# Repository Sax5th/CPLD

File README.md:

# CPLD
based on xilinx XC9536XL

Breakout Board Inspo:https://github.com/hotkeysoft/xc9536xlBreakout-kicad

C.O.T.S Version: http://dangerousprototypes.com/docs/XC9500XL_CPLD_breakout_board

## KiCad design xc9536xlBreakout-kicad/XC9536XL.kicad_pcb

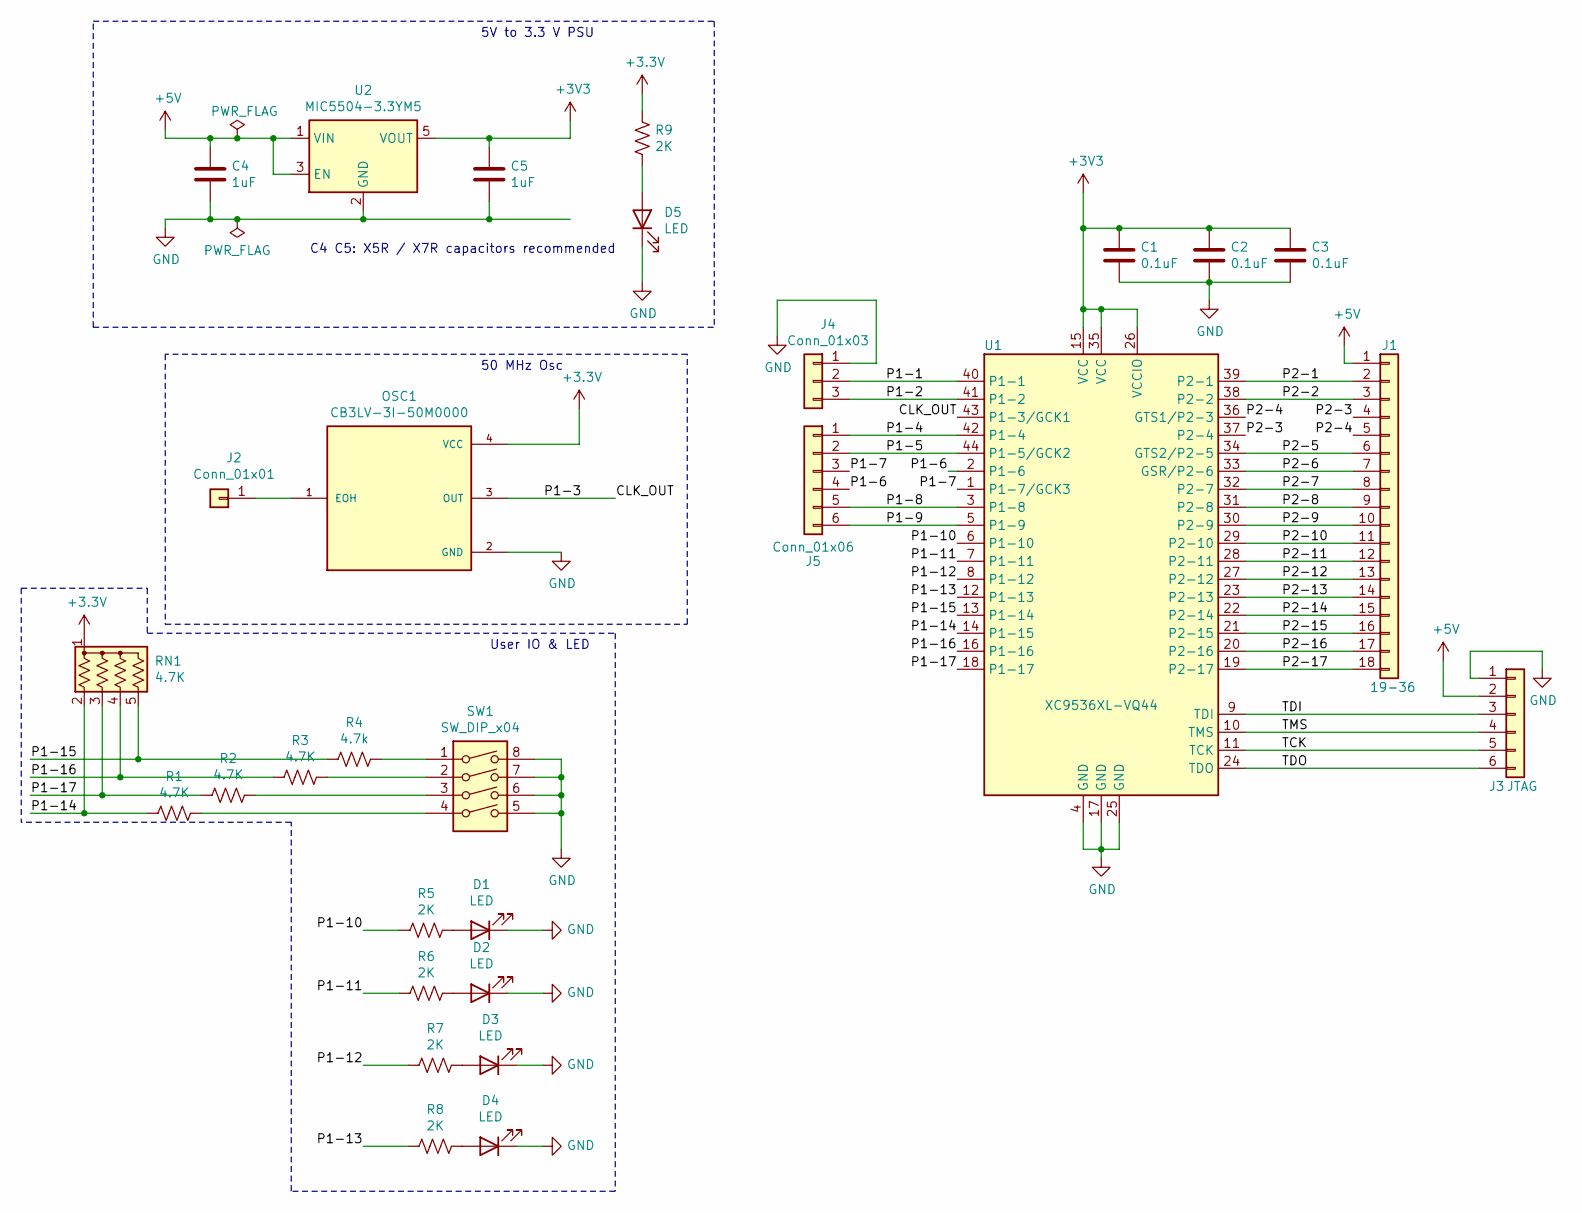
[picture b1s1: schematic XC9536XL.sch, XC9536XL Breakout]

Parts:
C1, C2, C3: 0.1uF; C_0603_1608Metric
C4, C5: 1uF; C_0603_1608Metric
D1, D2, D3, D4, D5: LED; D_0805_2012Metric_Pad1.15x1.40mm_HandSolder
J1: 19-36; PinHeader_1x18_P2.54mm_Vertical
J2: Conn_01x01; PinHeader_1x01_P2.54mm_Vertical
J3: JTAG; PinHeader_1x06_P2.54mm_Vertical
J4: Conn_01x03; PinHeader_1x03_P2.54mm_Vertical
J5: Conn_01x06; PinHeader_1x06_P2.54mm_Vertical
OSC1: CB3LV-3I-50M0000; OSCCC700X500X180-4N
R1, R2, R3: 4.7K; R_0805_2012Metric_Pad1.20x1.40mm_HandSolder
R4: 4.7k; R_0805_2012Metric_Pad1.20x1.40mm_HandSolder
R5, R6, R7, R8, R9: 2K; R_0805_2012Metric_Pad1.20x1.40mm_HandSolder
RN1: 4.7K; R_Array_Convex_4x1206
SW1: SW_DIP_x04; SW_DIP_SPSTx04_Slide_6.7x11.72mm_W8.61mm_P2.54mm_LowProfile
U1: XC9536XL-VQ44; TQFP-44_10x10mm_P0.8mm
U2: MIC5504-3.3YM5; SOT-23-5

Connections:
+5V: C4.1, J1.1, J3.2, U2.1 (VIN), U2.3 (EN)
/CLK_OUT: OSC1.3 (OUT), U1.43 (P1-3/GCK1)
/P1-1: J4.2, U1.40 (P1-1)
/P1-2: J4.3, U1.41 (P1-2)
/P1-4: J5.1, U1.42 (P1-4)
/P1-5: J5.2, U1.44 (P1-5/GCK2)
/P1-6: J5.4, U1.2 (P1-6)
/P1-7: J5.3, U1.1 (P1-7/GCK3)
/P1-8: J5.5, U1.3 (P1-8)
/P1-9: J5.6, U1.5 (P1-9)
/P1-10: R5.2, U1.6 (P1-10)
/P1-11: R6.2, U1.7 (P1-11)
/P1-12: R7.2, U1.8 (P1-12)
/P1-13: R8.2, U1.12 (P1-13)
/P1-14: R1.2, RN1.2 (R1), U1.14 (P1-15)
/P1-15: R4.2, RN1.5 (R4), U1.13 (P1-14)
/P1-16: R3.2, RN1.4 (R3), U1.16 (P1-16)
/P1-17: R2.2, RN1.3 (R2), U1.18 (P1-17)
/P2-1: J1.2, U1.39 (P2-1)
/P2-2: J1.3, U1.38 (P2-2)
/P2-3: J1.4, U1.37 (P2-4)
/P2-4: J1.5, U1.36 (GTS1/P2-3)
/P2-5: J1.6, U1.34 (GTS2/P2-5)
/P2-6: J1.7, U1.33 (GSR/P2-6)
/P2-7: J1.8, U1.32 (P2-7)
/P2-8: J1.9, U1.31 (P2-8)
/P2-9: J1.10, U1.30 (P2-9)
/P2-10: J1.11, U1.29 (P2-10)
/P2-11: J1.12, U1.28 (P2-11)
/P2-12: J1.13, U1.27 (P2-12)
/P2-13: J1.14, U1.23 (P2-13)
/P2-14: J1.15, U1.22 (P2-14)
/P2-15: J1.16, U1.21 (P2-15)
/P2-16: J1.17, U1.20 (P2-16)
/P2-17: J1.18, U1.19 (P2-17)
/TCK: J3.5, U1.11 (TCK)
/TDI: J3.3, U1.9 (TDI)
/TDO: J3.6, U1.24 (TDO)
/TMS: J3.4, U1.10 (TMS)
GND: C1.2, C2.2, C3.2, C4.2, C5.2, D1.1 (K), D2.1 (K), D3.1 (K), D4.1 (K), D5.1 (K), J3.1, J4.1, OSC1.2 (GND), SW1.5, SW1.6, SW1.7, SW1.8, U1.4 (GND), U1.17 (GND), U1.25 (GND), U2.2 (GND)
unnamed: D1.2 (A), R5.1
unnamed: D2.2 (A), R6.1
unnamed: D3.2 (A), R7.1
unnamed: D4.2 (A), R8.1
unnamed: D5.2 (A), R9.2
unnamed: J2.1, OSC1.1 (EOH)
unnamed: R1.1, SW1.4
unnamed: R2.1, SW1.3
unnamed: R3.1, SW1.2
unnamed: R4.1, SW1.1

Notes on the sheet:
C4 C5: X5R / X7R capacitors recommended
5V to 3.3 V PSU
50 MHz Osc
User IO & LED

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
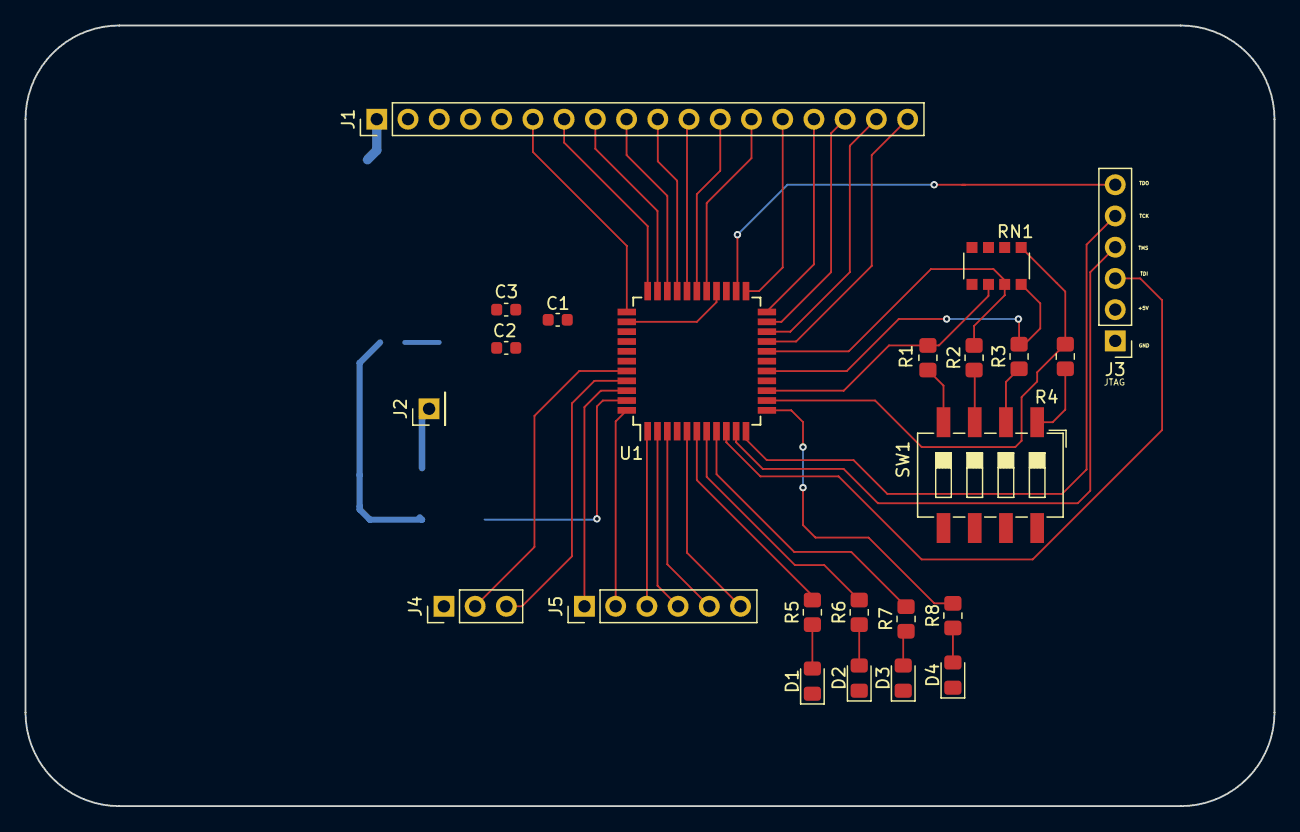
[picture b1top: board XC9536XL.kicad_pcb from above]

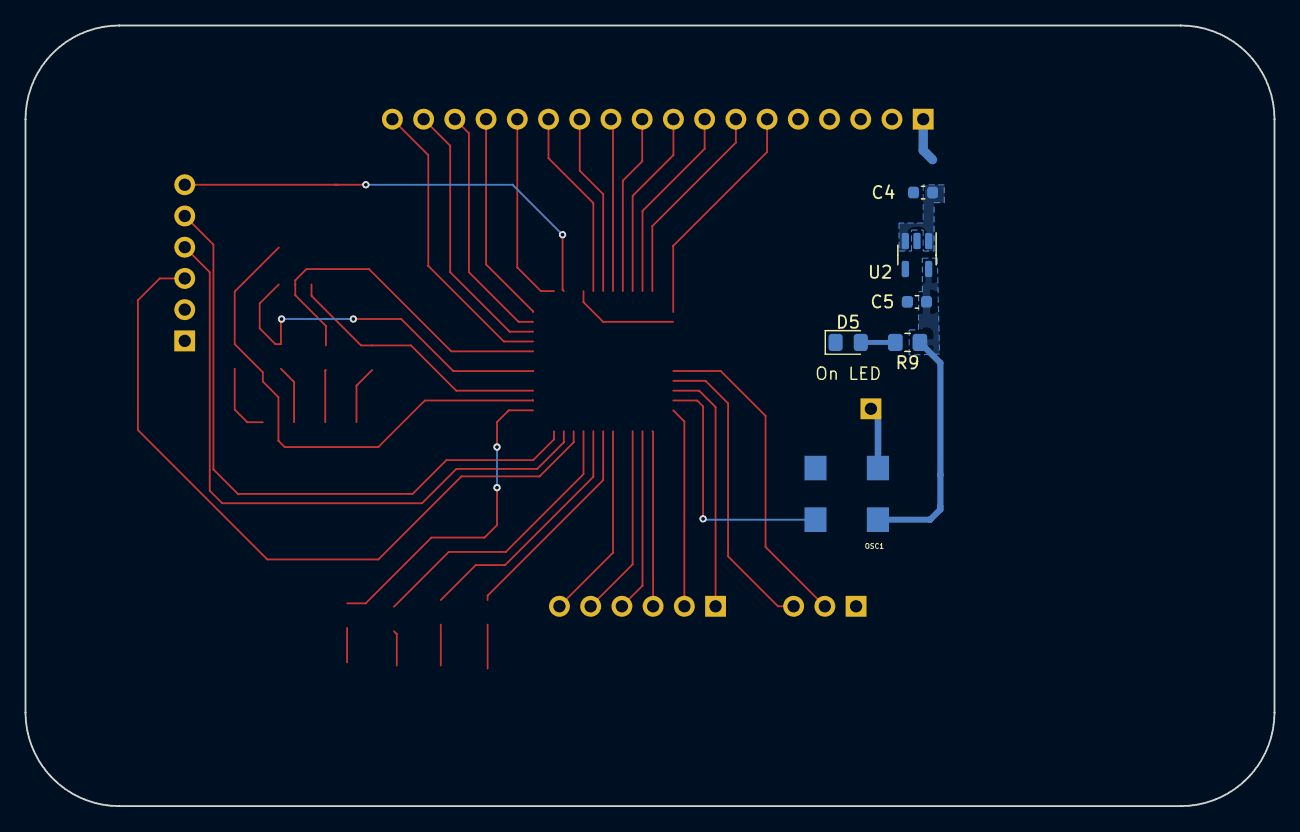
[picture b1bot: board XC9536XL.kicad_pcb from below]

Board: 2 copper layers, 101.6 x 63.5 mm, 29 parts (6 on the bottom side), 51 nets.

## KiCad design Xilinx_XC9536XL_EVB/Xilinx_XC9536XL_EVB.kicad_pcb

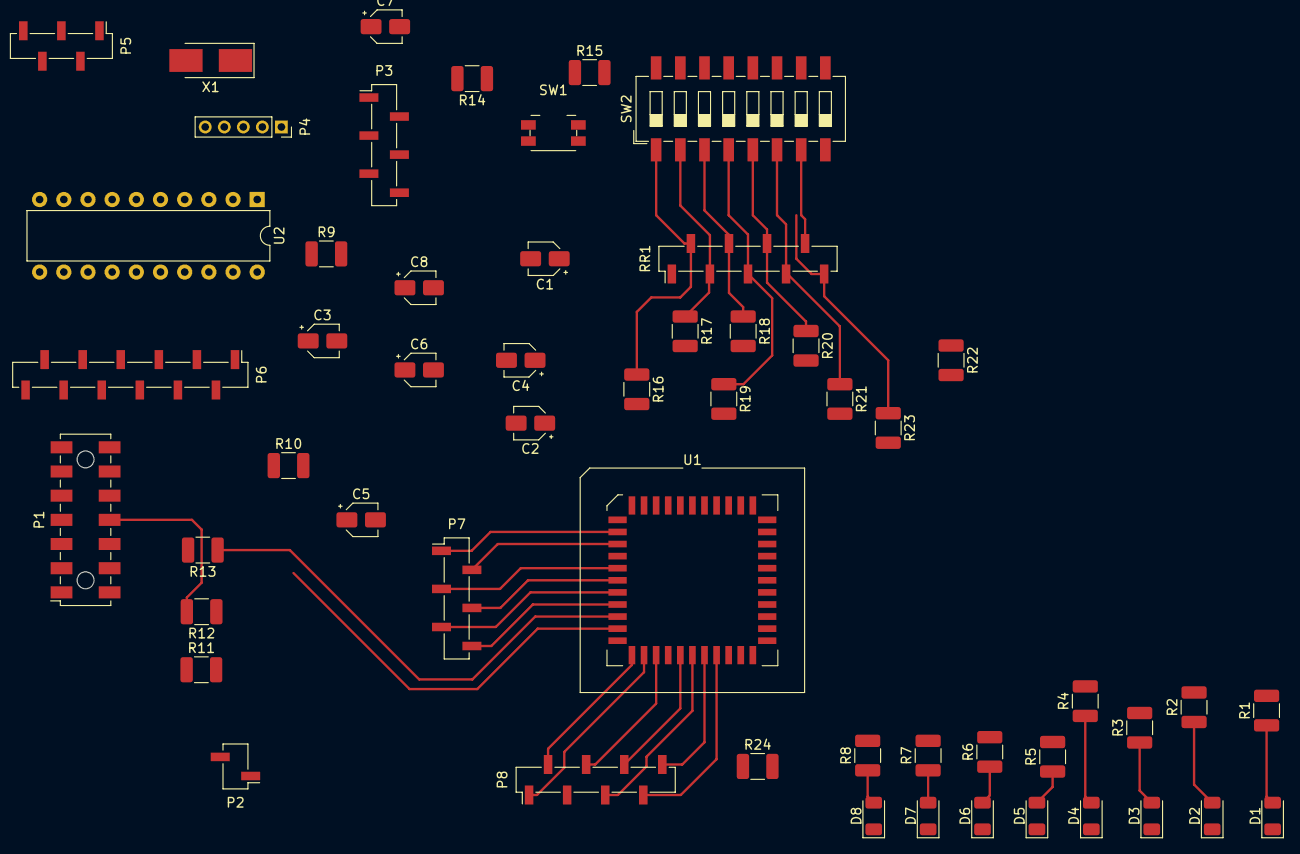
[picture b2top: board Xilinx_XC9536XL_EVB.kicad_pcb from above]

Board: 2 copper layers, 54 parts (0 on the bottom side), 75 nets.

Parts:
C1, C2, C3, C5, C6: 100n; CP_Elec_3x5.4
C4: 10uF; CP_Elec_3x5.4
C7, C8: 22p; CP_Elec_3x5.4
D1, D2, D3, D4, D5, D6, D7, D8: LED; LED_1206_3216Metric
P1: CONN_7X2; Samtec_HLE-107-02-xxx-DV-A_2x07_P2.54mm_Horizontal
P2: CONN_2; PinSocket_1x02_P2.00mm_Vertical_SMD_Pin1Left
P3: CONN_3X2; PinSocket_1x06_P2.00mm_Vertical_SMD_Pin1Left
P4: CONN_5; PinSocket_1x05_P2.00mm_Vertical
P5: CONN_5; PinSocket_1x05_P2.00mm_Vertical_SMD_Pin1Left
P6: CONN_12; PinSocket_1x12_P2.00mm_Vertical_SMD_Pin1Left
P7: CONN_6; PinSocket_1x06_P2.00mm_Vertical_SMD_Pin1Left
P8: CONN_8; PinSocket_1x08_P2.00mm_Vertical_SMD_Pin1Left
R1, R2, R3, R4, R5, R6, R7, R8: 330R; R_1210_3225Metric_Pad1.30x2.65mm_HandSolder
R9: 10k; R_1210_3225Metric_Pad1.30x2.65mm_HandSolder
R10, R11, R12, R13, R24: 0R; R_1210_3225Metric_Pad1.30x2.65mm_HandSolder
R14, R15, R16, R17, R18, R19, R20, R21, R22, R23: 4k7; R_1210_3225Metric_Pad1.30x2.65mm_HandSolder
RR1: 4k7; PinSocket_1x09_P2.00mm_Vertical_SMD_Pin1Left
SW1: SW_PUSH; Panasonic_EVQPUJ_EVQPUA
SW2: SW_DIP_8; SW_DIP_SPSTx08_Slide_6.7x21.88mm_W8.61mm_P2.54mm_LowProfile
U1: XC9536XLPC44; PLCC-44_SMD-Socket
U2: ATtiny2313-20PU; DIP-20_W7.62mm
X1: XTAL; Crystal_SMD_5032-2Pin_5.0x3.2mm_HandSoldering

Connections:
+3.3V: C1.1, C2.1, C3.1, C4.1, P2.1, P4.1, P8.3, R10.1, R24.1, RR1.1, SW1.2, U1.21, U1.32, U1.41
/3V3P: C6.1, P3.2, P6.1, R9.1, R10.2, R11.2, U2.20
/L1: R1.2, U1.36
/L2: R2.2, U1.35
/L3: R3.2, U1.34
/L4: R4.2, U1.33
/L5: R5.2, U1.29
/L6: R6.2, U1.28
/L7: R7.2, U1.27
/L8: R8.2, U1.26
/MISO: P3.1, P6.3, U1.4, U2.18
/MOSI: P3.4, P6.4, U1.6, U2.17
/O1: P8.1, U1.19
/O2: P8.2, U1.18
/O3: P8.4, U1.20
/O4: P8.6, U1.22
/O5: P8.7, U1.25
/O6: P8.8, U1.24
/PD6: P6.10, U2.11
/RESET: P3.5, P4.2, R9.2, U1.2, U2.1
/S1: R16.2, U1.44
/S2: R17.2, U1.1
/S3: R18.2, U1.42
/S4: R19.2, U1.43
/S5: R20.2, U1.40
/S6: R21.2, U1.39
/S7: R22.2, U1.38
/S8: R23.2, U1.37
/SCK: P3.3, P6.2, U1.5, U2.19
/TCK: P1.6, U1.17
/TDI: R13.1, U1.15
/TDO: R12.1, U1.30
/TMS: P1.4, U1.16
GND: C1.2, C2.2, C3.2, C4.2, C5.2, C6.2, C7.2, C8.2, P1.1, P1.3, P1.5, P1.7, P1.9, P1.11, P1.13, P2.2, P3.6, P4.5, P5.5, P6.11, P6.12, P8.5, R14.2, SW2.9, SW2.10, SW2.11, SW2.12, SW2.13, SW2.14, SW2.15, SW2.16, U1.10, U1.23, U1.31, U2.10
unnamed: C5.1, P1.2, R11.1
unnamed: C7.1, U2.4, X1.1
unnamed: C8.1, U2.5, X1.2
unnamed: D1.1, D2.1, D3.1, D4.1, D5.1, D6.1, D7.1, D8.1, R24.2
unnamed: D1.2, R1.1
unnamed: D2.2, R2.1
unnamed: D3.2, R3.1
unnamed: D4.2, R4.1
unnamed: D5.2, R5.1
unnamed: D6.2, R6.1
unnamed: D7.2, R7.1
unnamed: D8.2, R8.1
unnamed: P1.8, R12.2
unnamed: P1.10, R13.2
unnamed: P4.3, U2.2
unnamed: P4.4, U2.3
unnamed: P5.1, U2.6
unnamed: P5.2, U2.7
unnamed: P5.3, U2.8
unnamed: P5.4, U2.9
unnamed: P6.5, U1.7, U2.16
unnamed: P6.6, U2.15
unnamed: P6.7, U2.14
unnamed: P6.8, U2.13
unnamed: P6.9, U2.12
unnamed: P7.1, U1.8
unnamed: P7.2, U1.9
unnamed: P7.3, U1.11
unnamed: P7.4, U1.12
unnamed: P7.5, U1.13
unnamed: P7.6, U1.14
unnamed: R14.1, R15.1, SW1.1
unnamed: R15.2, U1.3
unnamed: R16.1, RR1.2, SW2.1
unnamed: R17.1, RR1.3, SW2.2
unnamed: R18.1, RR1.4, SW2.3
unnamed: R19.1, RR1.5, SW2.4
unnamed: R20.1, RR1.6, SW2.5
unnamed: R21.1, RR1.7, SW2.6
unnamed: R22.1, RR1.8, SW2.7
unnamed: R23.1, RR1.9, SW2.8

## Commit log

2021-04-19 Add files via upload
    Initial commit 4.19
2021-06-03 Add files via upload
    6.3 Commit
2021-06-03 Add files via upload
    Work Update
    Schematics finished
    - add new footprints
    -start layout
2021-06-05 Add files via upload
    -schematics complete
    - start of layout
2021-06-11 Add files via upload
    6.9.21 After Design Review
    Notes
    Check forward current/ voltage on LEDs
    reassign led resistor values to be lower
    throw in some other sized caps for vcc
    make caps as close as possible to each power pin
2021-06-14 Add files via upload
    Commit Gerbs for lpkf
2021-06-14 Add files via upload
    gerb_zip
2021-06-14 Add files via upload
    gerbs for lpkf
